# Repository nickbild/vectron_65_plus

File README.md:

# Vectron 65 Plus

The Vectron 65 Plus is a 6502 CPU-based computer with keyboard support that can run BASIC.  It is highly extensible via 32 GPIO pins.

At present, I have built the following peripherals for the computer:
- [Vectron VGA Plus v2](https://github.com/nickbild/vectron_vga_plus_v2) - VGA output with pixel-level control
- [Vectron VGA Plus Text Mode](https://github.com/nickbild/vectron_vga_plus_text_mode) - Add-on for Vectron VGA Plus v2 that simplifies displaying text on screen
- [Vectron Sound Plus](https://github.com/nickbild/vectron_sound_plus) - Audio output with the AY-3-8910 sound generator chip

Read on for demonstrations of each of these add-ons.

This is an enhanced version of my [Vectron 65](https://github.com/nickbild/vectron_65) computer.

## How It Works

At the heart of the system is a WDC 65C02 CPU running at 8 MHz.  32 KB of SRAM is available, and a 32 KB ROM chip stores the program to execute (you can burn the ROM with [my Arduino code](https://github.com/nickbild/eeprom_burner_mega)).  A pair of 6522 VIA chips add a total of 32 GPIO pins to interface with external peripherals.  A PS/2 connector is present to support a keyboard (or a mouse, in theory, though I haven't tried one yet) — the clock and data lines are routed to GPIO pins.

This is the circuit design:

## Media

Here, the Vectron 65 Plus (left) is running TinyBASIC.  On the right, [Vectron VGA Plus Text Mode](https://github.com/nickbild/vectron_vga_plus_text_mode) is stacked on top of [Vectron VGA Plus v2](https://github.com/nickbild/vectron_vga_plus_v2) to provide a text mode VGA display output ([6502 code here](https://github.com/nickbild/vectron_65_plus/blob/main/os_vvga.asm)):

In this example, the Vectron 65 Plus (right) is hooked up to [Vectron VGA Plus v2](https://github.com/nickbild/vectron_vga_plus_v2) to output some bitmap graphics ([6502 code here](https://github.com/nickbild/vectron_65_plus/blob/main/pacman.asm)):

And for audio, I added in the [Vectron Sound Plus](https://github.com/nickbild/vectron_sound_plus) module:

You can download an [MP3 here](https://github.com/nickbild/vectron_sound_plus/blob/main/media/vectron_65_audio.mp3?raw=true) of a tune I made with it.

And a few more pictures:

## Bill of Materials

- 1 x 65C02 CPU
- 2 x 6522 VIA
- 1 x 28C256 ROM
- 1 x AS6C62256A RAM
- 4 x 74682
- 1 x 7404
- 1 x 7408
- 1 x 7432
- 1 x 8 MHz crystal oscillator
- 1 x push button
- 4 x 3.3K resistors
- 2 x 5.1K resistors
- 2 x 10K resistors
- 3 x 47 uF electrolytic capacitors
- 14 x 0.1 uF ceramic capacitors
- 1 x PS/2 connector
- 1 x PCB ([Kicad design file here](https://github.com/nickbild/vectron_65_plus/tree/main/kicad_vectron_65_plus))

## About the Author

[Nick A. Bild, MS](https://nickbild79.firebaseapp.com/#!/)

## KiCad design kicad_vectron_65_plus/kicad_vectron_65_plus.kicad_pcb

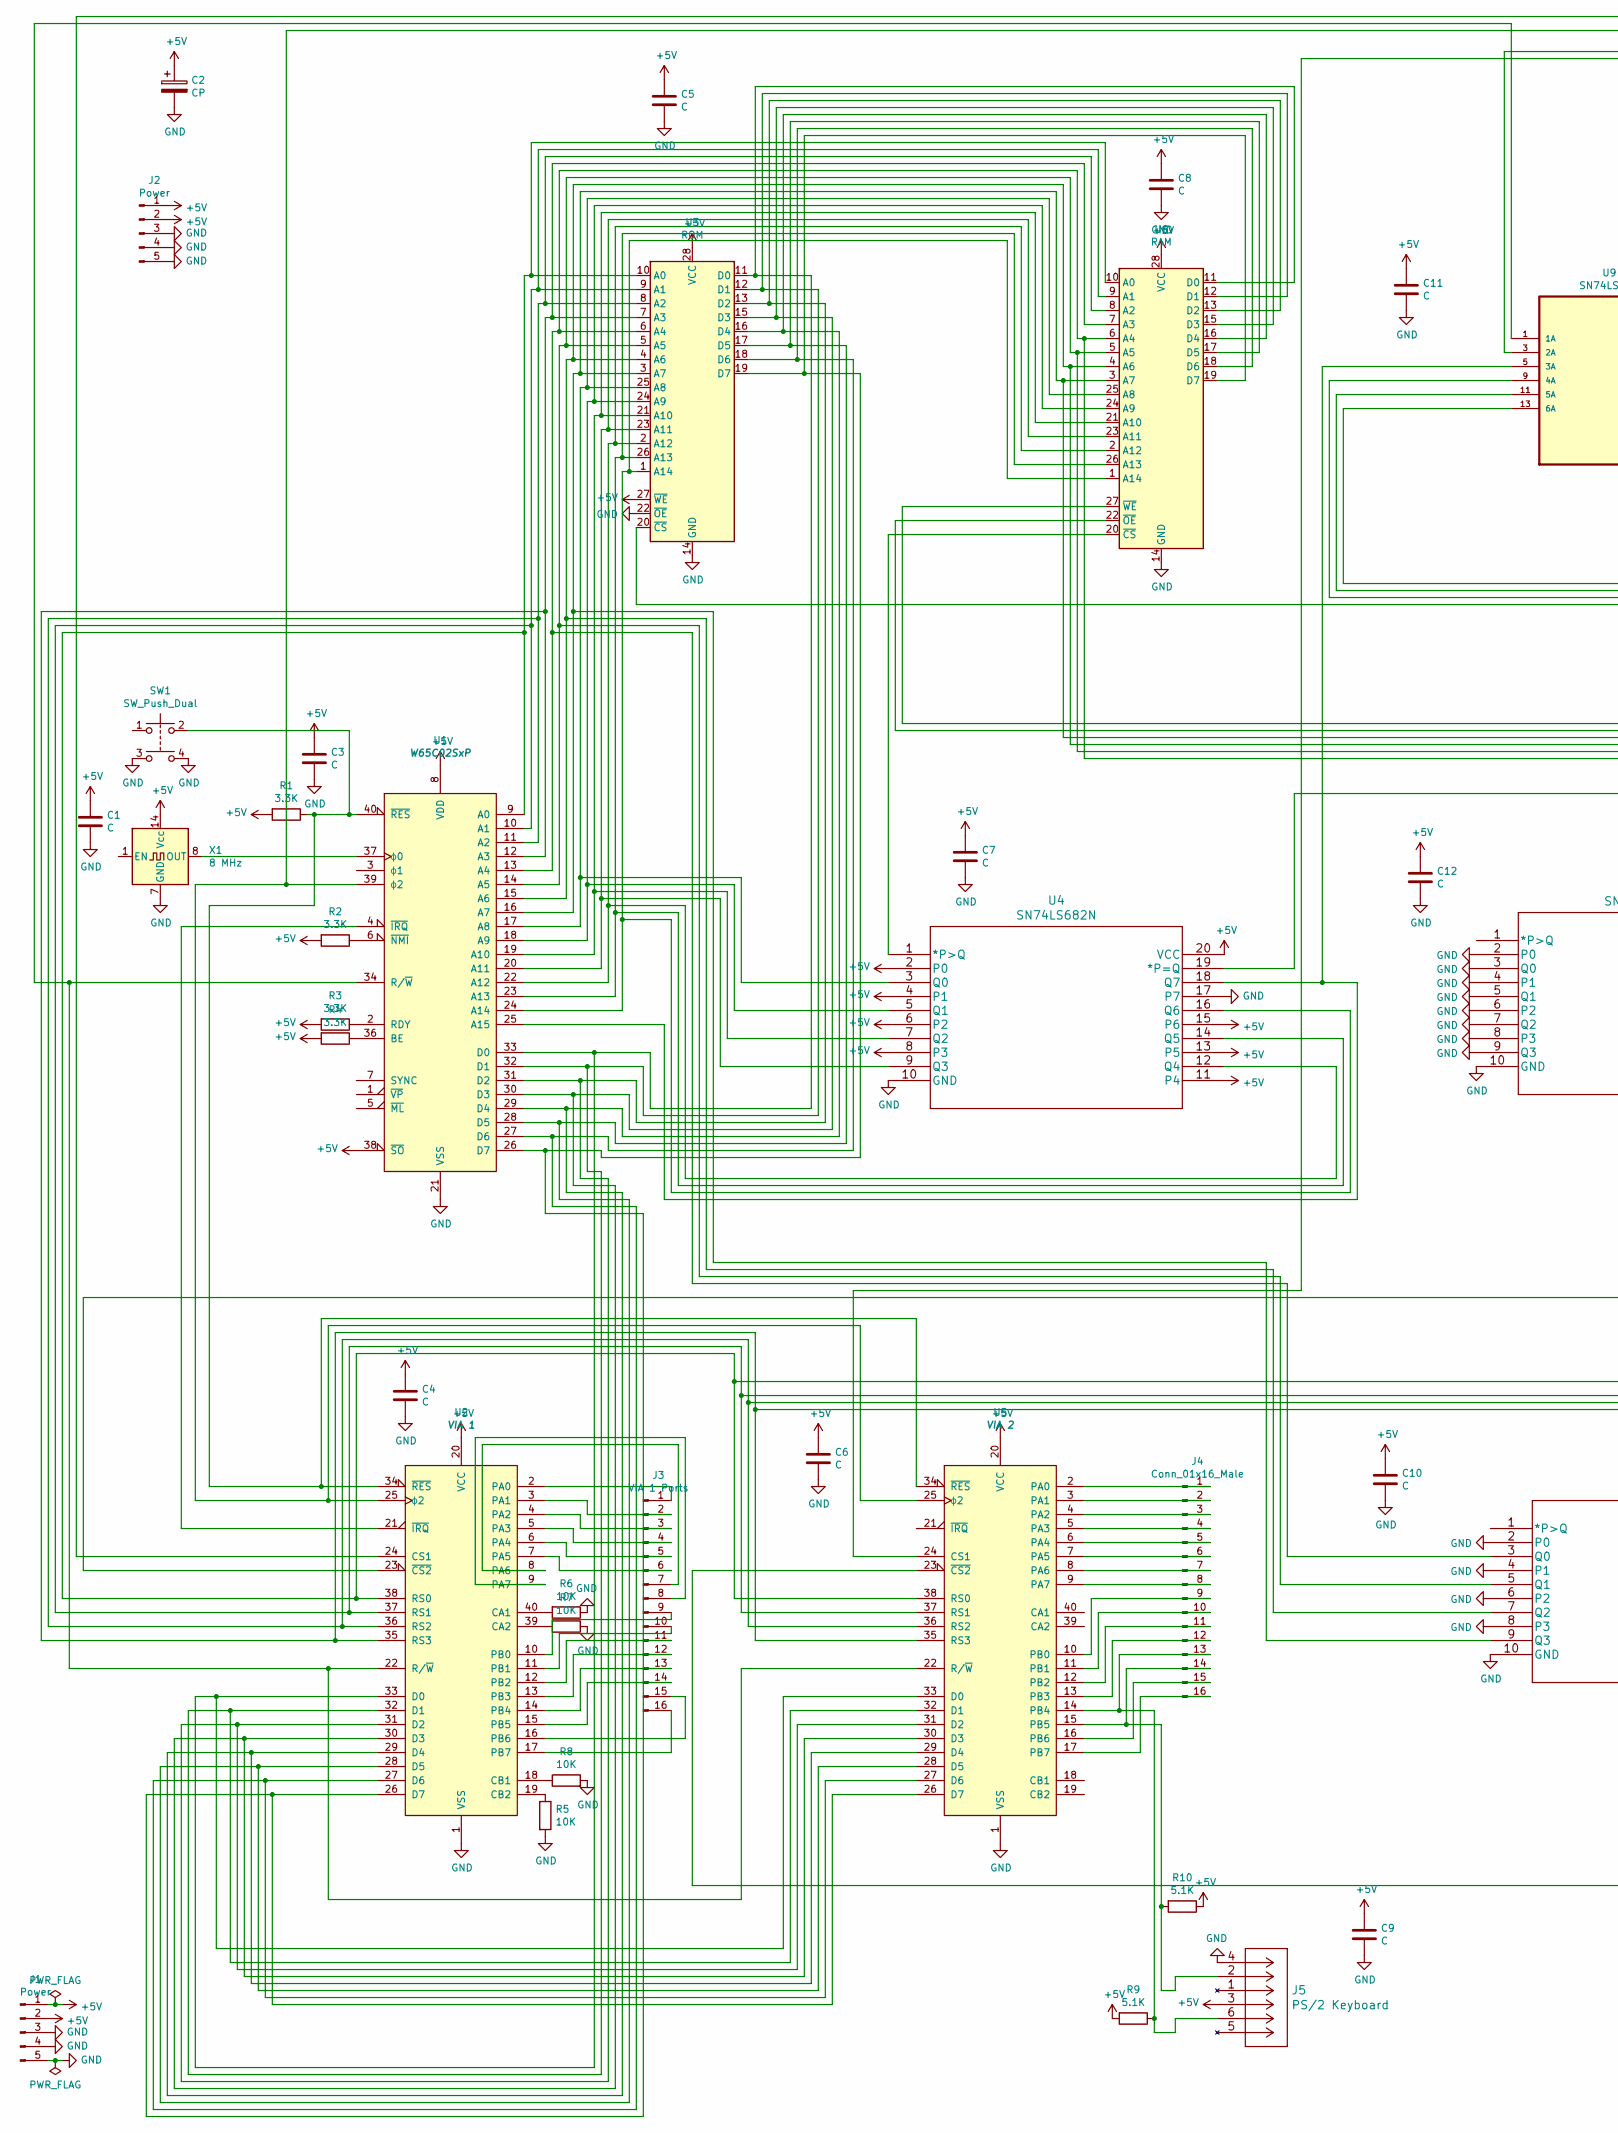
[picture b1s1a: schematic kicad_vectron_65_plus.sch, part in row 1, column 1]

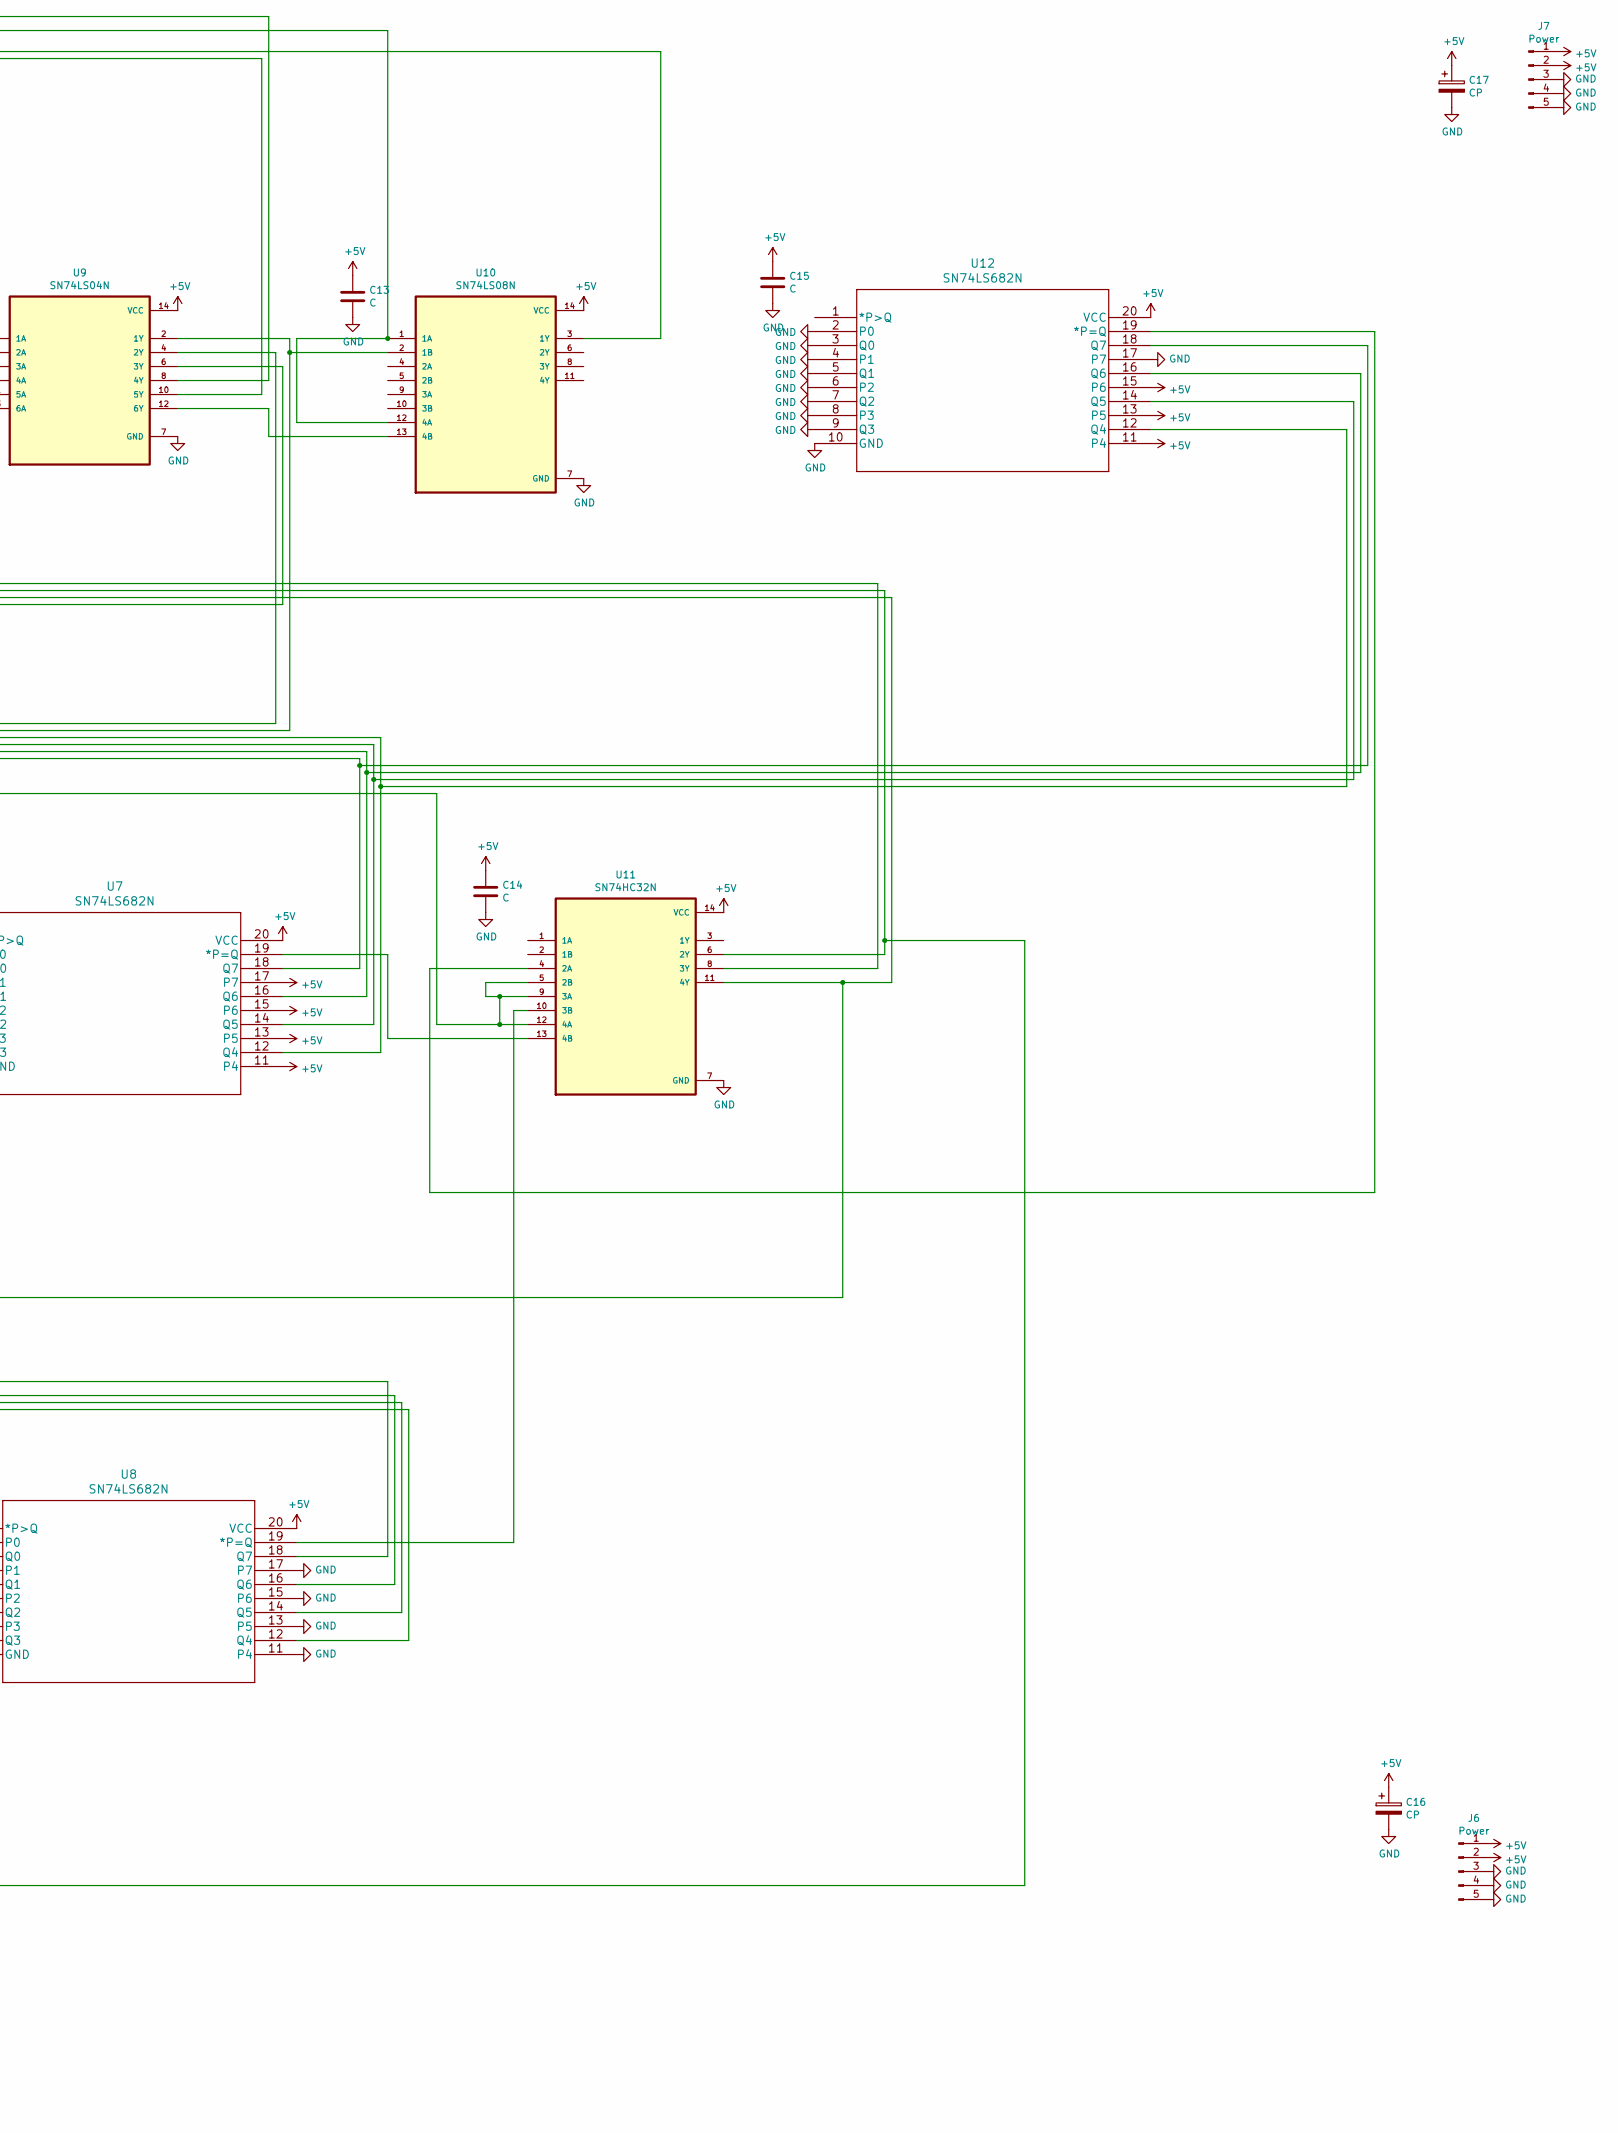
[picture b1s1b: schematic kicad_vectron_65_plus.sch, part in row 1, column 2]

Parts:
C1, C3, C4, C5, C6, C7, C8, C9, C10, C11, C12, C13, C14, C15: C; C_Disc_D3.0mm_W2.0mm_P2.50mm
C2, C16, C17: CP; CP_Radial_D8.0mm_P5.00mm
J1, J2, J6, J7: Power; PinHeader_1x05_P2.54mm_Vertical
J3: VIA 1 Ports; PinHeader_1x16_P2.54mm_Vertical
J4: Conn_01x16_Male; PinHeader_1x16_P2.54mm_Vertical
J5: PS/2 Keyboard; 5750071-1
R1, R2, R3, R4: 3.3K; R_Axial_DIN0204_L3.6mm_D1.6mm_P5.08mm_Horizontal
R5, R6, R7, R8: 10K; R_Axial_DIN0204_L3.6mm_D1.6mm_P5.08mm_Horizontal
R9, R10: 5.1K; R_Axial_DIN0204_L3.6mm_D1.6mm_P5.08mm_Horizontal
SW1: SW_Push_Dual; SW_TH_Tactile_Omron_B3F-10xx
U1: W65C02SxP; DIP-40_W15.24mm
U2: VIA 1; DIP-40_W15.24mm
U3: ROM; DIP-28_W15.24mm
U4, U7, U8, U12: SN74LS682N; DIP-20_W7.62mm
U5: VIA 2; DIP-40_W15.24mm
U6: RAM; DIP-28_W15.24mm
U9: SN74LS04N; DIP-14_W7.62mm
U10: SN74LS08N; DIP-14_W7.62mm
U11: SN74HC32N; DIP-14_W7.62mm
X1: 8 MHz; Oscillator_DIP-14

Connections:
+5V: C1.1, C2.1, C3.1, C4.1, C5.1, C6.1, C7.1, C8.1, C9.1, C10.1, C11.1, C12.1, C13.1, C14.1, C15.1, C16.1, C17.1, J1.1, J1.2, J2.1, J2.2, J5.3, J6.1, J6.2, J7.1, J7.2, R1.2, R2.2, R3.2, R4.2, R9.2, R10.1, U1.8 (VDD), U1.38 (~SO), U2.20 (VCC), U3.27 (~WE), U3.28 (VCC), U4.2 (P0), U4.4 (P1), U4.6 (P2), U4.8 (P3), U4.11 (P4), U4.13 (P5), U4.15 (P6), U4.20 (VCC), U5.20 (VCC), U6.28 (VCC), U7.11 (P4), U7.13 (P5), U7.15 (P6), U7.17 (P7), U7.20 (VCC), U8.20 (VCC), U9.14 (VCC), U10.14 (VCC), U11.14 (VCC), U12.11 (P4), U12.13 (P5), U12.15 (P6), U12.20 (VCC), X1.14 (Vcc)
GND: C1.2, C2.2, C3.2, C4.2, C5.2, C6.2, C7.2, C8.2, C9.2, C10.2, C11.2, C12.2, C13.2, C14.2, C15.2, C16.2, C17.2, J1.3, J1.4, J1.5, J2.3, J2.4, J2.5, J5.4, J6.3, J6.4, J6.5, J7.3, J7.4, J7.5, R5.2, R6.1, R7.1, R8.2, SW1.3, SW1.4, U1.21 (VSS), U2.1 (VSS), U3.14 (GND), U3.22 (~OE), U4.10 (GND), U4.17 (P7), U5.1 (VSS), U6.14 (GND), U7.2 (P0), U7.3 (Q0), U7.4 (P1), U7.5 (Q1), U7.6 (P2), U7.7 (Q2), U7.8 (P3), U7.9 (Q3), U7.10 (GND), U8.2 (P0), U8.4 (P1), U8.6 (P2), U8.8 (P3), U8.10 (GND), U8.11 (P4), U8.13 (P5), U8.15 (P6), U8.17 (P7), U9.7 (GND), U10.7 (GND), U11.7 (GND), U12.2 (P0), U12.3 (Q0), U12.4 (P1), U12.5 (Q1), U12.6 (P2), U12.7 (Q2), U12.8 (P3), U12.9 (Q3), U12.10 (GND), U12.17 (P7), X1.7 (GND)
unnamed: J3.1, U2.2 (PA0)
unnamed: J3.2, U2.3 (PA1)
unnamed: J3.3, U2.4 (PA2)
unnamed: J3.4, U2.5 (PA3)
unnamed: J3.5, U2.6 (PA4)
unnamed: J3.6, U2.7 (PA5)
unnamed: J3.7, U2.8 (PA6)
unnamed: J3.8, U2.9 (PA7)
unnamed: J3.9, U2.10 (PB0)
unnamed: J3.10, U2.11 (PB1)
unnamed: J3.11, U2.12 (PB2)
unnamed: J3.12, U2.13 (PB3)
unnamed: J3.13, U2.14 (PB4)
unnamed: J3.14, U2.15 (PB5)
unnamed: J3.15, U2.16 (PB6)
unnamed: J3.16, U2.17 (PB7)
unnamed: J4.1, U5.2 (PA0)
unnamed: J4.2, U5.3 (PA1)
unnamed: J4.3, U5.4 (PA2)
unnamed: J4.4, U5.5 (PA3)
unnamed: J4.5, U5.6 (PA4)
unnamed: J4.6, U5.7 (PA5)
unnamed: J4.7, U5.8 (PA6)
unnamed: J4.8, U5.9 (PA7)
unnamed: J4.9, U5.10 (PB0)
unnamed: J4.10, U5.11 (PB1)
unnamed: J4.11, U5.12 (PB2)
unnamed: J4.12, U5.13 (PB3)
unnamed: J4.13, J5.6, R9.1, U5.14 (PB4)
unnamed: J4.14, J5.2, R10.2, U5.15 (PB5)
unnamed: J4.15, U5.16 (PB6)
unnamed: J4.16, U5.17 (PB7)
unnamed: R1.1, SW1.2, U1.40 (~RES), U2.34 (~RES), U5.34 (~RES)
unnamed: R2.1, U1.6 (~NMI)
unnamed: R3.1, U1.2 (RDY)
unnamed: R4.1, U1.36 (BE)
unnamed: R5.1, U2.19 (CB2)
unnamed: R6.2, U2.40 (CA1)
unnamed: R7.2, U2.39 (CA2)
unnamed: R8.1, U2.18 (CB1)
unnamed: U1.4 (~IRQ), U2.21 (~IRQ)
unnamed: U1.9 (A0), U2.38 (RS0), U3.10 (A0), U5.38 (RS0), U6.10 (A0), U8.18 (Q7)
unnamed: U1.10 (A1), U2.37 (RS1), U3.9 (A1), U5.37 (RS1), U6.9 (A1), U8.16 (Q6)
unnamed: U1.11 (A2), U2.36 (RS2), U3.8 (A2), U5.36 (RS2), U6.8 (A2), U8.14 (Q5)
unnamed: U1.12 (A3), U2.35 (RS3), U3.7 (A3), U5.35 (RS3), U6.7 (A3), U8.12 (Q4)
unnamed: U1.13 (A4), U3.6 (A4), U6.6 (A4), U7.18 (Q7), U8.3 (Q0), U12.18 (Q7)
unnamed: U1.14 (A5), U3.5 (A5), U6.5 (A5), U7.16 (Q6), U8.5 (Q1), U12.16 (Q6)
unnamed: U1.15 (A6), U3.4 (A6), U6.4 (A6), U7.14 (Q5), U8.7 (Q2), U12.14 (Q5)
unnamed: U1.16 (A7), U3.3 (A7), U6.3 (A7), U7.12 (Q4), U8.9 (Q3), U12.12 (Q4)
unnamed: U1.17 (A8), U3.25 (A8), U4.3 (Q0), U6.25 (A8)
unnamed: U1.18 (A9), U3.24 (A9), U4.5 (Q1), U6.24 (A9)
unnamed: U1.19 (A10), U3.21 (A10), U4.7 (Q2), U6.21 (A10)
unnamed: U1.20 (A11), U3.23 (A11), U4.9 (Q3), U6.23 (A11)
unnamed: U1.22 (A12), U3.2 (A12), U4.12 (Q4), U6.2 (A12)
unnamed: U1.23 (A13), U3.26 (A13), U4.14 (Q5), U6.26 (A13)
unnamed: U1.24 (A14), U3.1 (A14), U4.16 (Q6), U6.1 (A14)
unnamed: U1.25 (A15), U4.18 (Q7), U9.5 (3A)
unnamed: U1.26 (D7), U2.26 (D7), U3.19 (D7), U5.26 (D7), U6.19 (D7)
unnamed: U1.27 (D6), U2.27 (D6), U3.18 (D6), U5.27 (D6), U6.18 (D6)
unnamed: U1.28 (D5), U2.28 (D5), U3.17 (D5), U5.28 (D5), U6.17 (D5)
unnamed: U1.29 (D4), U2.29 (D4), U3.16 (D4), U5.29 (D4), U6.16 (D4)
unnamed: U1.30 (D3), U2.30 (D3), U3.15 (D3), U5.30 (D3), U6.15 (D3)
unnamed: U1.31 (D2), U2.31 (D2), U3.13 (D2), U5.31 (D2), U6.13 (D2)
unnamed: U1.32 (D1), U2.32 (D1), U3.12 (D1), U5.32 (D1), U6.12 (D1)
unnamed: U1.33 (D0), U2.33 (D0), U3.11 (D0), U5.33 (D0), U6.11 (D0)
unnamed: U1.34 (R/~W), U2.22 (R/~W), U5.22 (R/~W), U9.1 (1A)
unnamed: U1.37 (ϕ0), X1.8 (OUT)
unnamed: U1.39 (ϕ2), U2.25 (ϕ2), U5.25 (ϕ2), U10.1 (1A), U10.12 (4A)
unnamed: U2.24 (CS1), U9.8 (4Y)
unnamed: U3.20 (~CS), U9.6 (3Y)
unnamed: U4.1 (*P>Q), U6.20 (~CS)
unnamed: U5.24 (CS1), U9.10 (5Y)
unnamed: U6.27 (~WE), U9.4 (2Y)
unnamed: U6.22 (~OE), U9.2 (1Y), U10.2 (1B)
unnamed: U9.3 (2A), U10.3 (1Y)
unnamed: U9.12 (6Y), U10.13 (4B)
unnamed: U11.4 (2A), U12.19 (*P=Q)
unnamed: U5.23 (~CS2), U9.11 (5A), U11.6 (2Y)
unnamed: U9.13 (6A), U11.8 (3Y)
unnamed: U8.19 (*P=Q), U11.10 (3B)
unnamed: U2.23 (~CS2), U9.9 (4A), U11.11 (4Y)
unnamed: U4.19 (*P=Q), U11.5 (2B), U11.9 (3A), U11.12 (4A)
unnamed: U7.19 (*P=Q), U11.13 (4B)

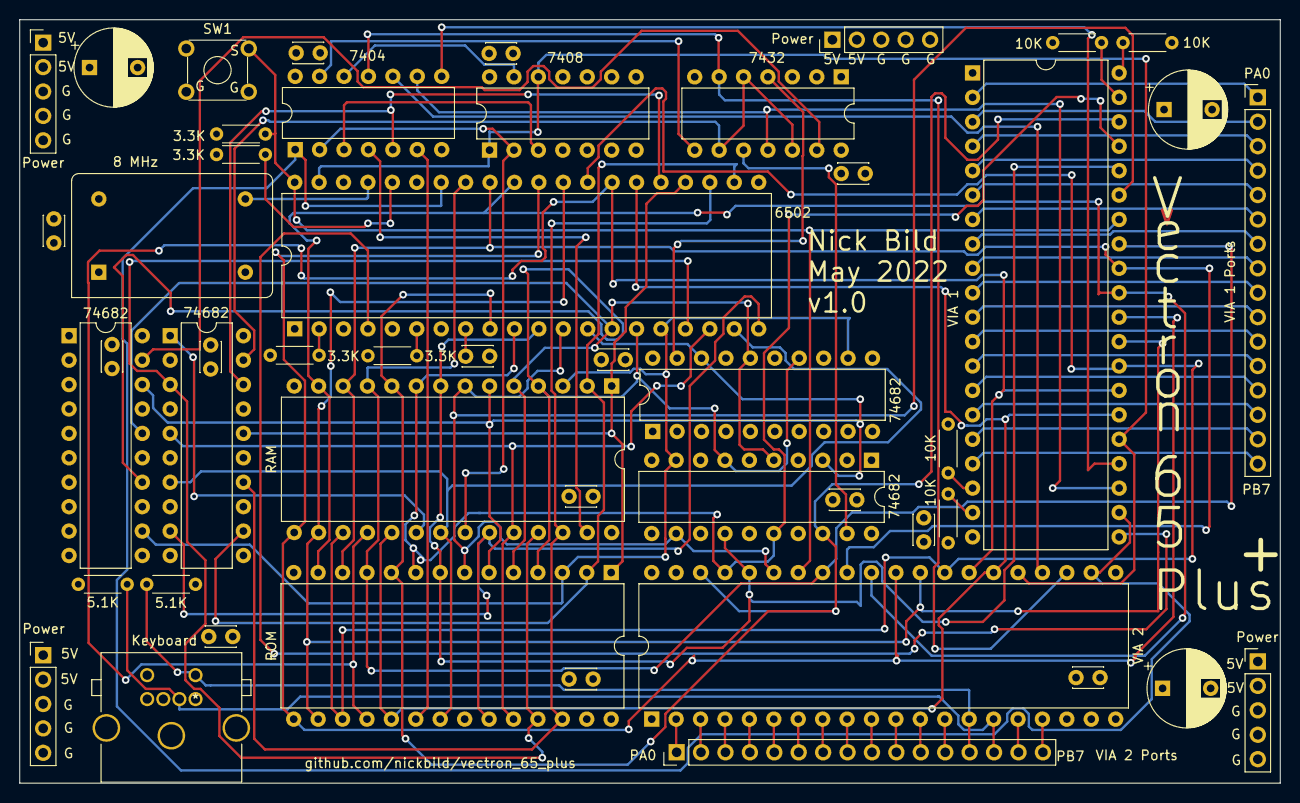
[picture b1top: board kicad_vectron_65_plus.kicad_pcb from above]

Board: 4 copper layers, 131.1 x 79.4 mm, 48 parts (0 on the bottom side), 85 nets.

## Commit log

2020-11-23 Initial commit.
2020-11-23 SD Card use POC on Pi.
2020-11-23 Update POC.
2020-11-24 Raw SD read/write working.
2020-11-24 Rename to indicate this is for SD cards.
2020-11-26 Add AY-3-8910 raw control POC.
2020-12-04 Finalize audio POC.
2020-12-07 Add build tools.
2020-12-07 First test of audio.
2020-12-16 Generate all sounds.
2020-12-16 Add wav saving.
2020-12-16 Switch WAV write method.
2020-12-18 Build full pipeline.
2021-08-31 Clean up and add PicoROM support.
2021-09-12 Fix timing on block write.
2021-11-05 Add TeensyROM build code.
2021-11-05 Fix data type.
2021-11-06 Add startup sound.
2022-02-12 Modify OS for Vectron VGA Plus.
2022-02-13 Update for Vectron VGA output.
2022-02-13 Modify OS for Vectron VGA.
2022-02-17 Fix BASIC output timings and pad character.
2022-02-17 Adjust starting column number.
2022-02-18 Fix horizontal scrolling.
2022-02-19 Adjust for speed-optimized text mode version.
2022-02-19 Save progress.
2022-02-21 Resize screen and fix backspace.
2022-02-22 Speed up screen redraws by skipping identical characters.
2022-02-26 Update for VVGA 2.0.
2022-04-24 Speed up text writes.
2022-05-02 Save progress on schematic.
2022-05-09 Update schematic.
2022-05-13 Save progress on PCB.
2022-05-14 Adjust for 8 MHz.
2022-05-31 Begin work on Pong.
2022-06-08 Save progress on Pong.
2022-06-10 Begin adding keyboard support.
2022-06-15 Update documentation.
2022-06-15 Mirror image for PS/2 connection.
2022-06-16 Switch to using controller.
2022-06-17 Add bounds to paddle 2 movement.
2022-06-17 Ensure full paddle draw takes place.
2022-06-24 Add pacman characters.
2022-06-24 Ghost looks good.
2022-06-25 Ghosts finished.

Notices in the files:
parts and their libraries:
Copyright 2021 Accelerated Designs. All rights reserved.
